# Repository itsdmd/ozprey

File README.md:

# Ozprey - A remix of [osprey-remix](https://github.com/kapee1/osprey-remix)

## Changes compared to the original Osprey

-   Remove cutout under MCU to allow more flexible PCB trace routing.
-   Remove battery holder cutout, replace onboard battery connector socket with battery connector pads.
    -   These changes were made since I want to use a large Li-Po battery placed under the PCB.
-   Simplify top edge, widen the split gap to accomodate changed switch footprint.
-   Replace power and reset switch footprint. Schematics for both can be found inside [img](./img) folder.
-   Adjust onboard M2 mounting holes' position.

These changes made the board incompatible with the original case & plate. You can get the [.STEP file](./ozprey_case/osprey_pcb.step) and design your own case & plate.

## Thanks

Huge thanks to [ebastler](https://github.com/ebastler), author of the [original project](https://github.com/ebastler/osprey) for the inspiration and design, and [kapee1](https://github.com/kapee1) for the nice!nano implementation with the [osprey-remix](https://github.com/kapee1/osprey-remix).

The keyboard switch footprint was from [daprice/keyswitches.pretty](https://github.com/daprice/keyswitches.pretty).

## Disclaimer

This is a **personal project** and not affiliated with the original authors. Due to the changes, the board is not compatible with the original case and plate.

The gerber file has been checked against JLCPCB's DFM checker and no critical error was found. All files are provided as-is, **without any warranty or support**. Use at your own risk.

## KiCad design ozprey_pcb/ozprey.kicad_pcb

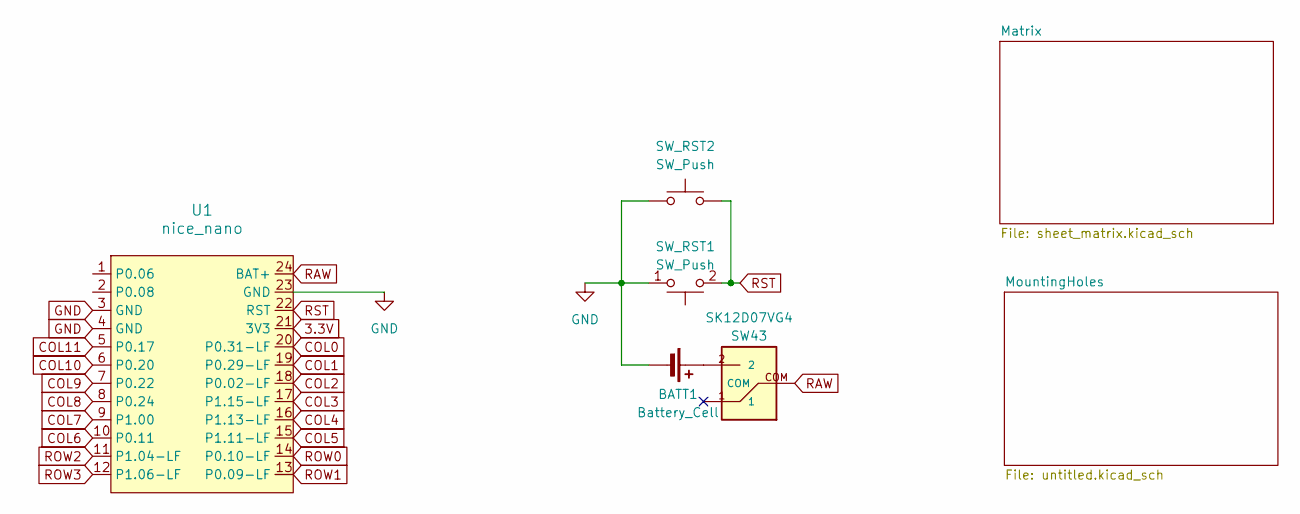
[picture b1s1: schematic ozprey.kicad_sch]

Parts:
BATT1: Battery_Cell; Battery_Pads-dual-side
SW43: SK12D07VG4; SW-S_SK12D07VG4
SW_RST1: SW_Push; SW-S_7.4x2.6-4pad-smd
SW_RST2: SW_Push; SW-T_SPST_TL3342
U1: nice_nano; MCB_nice-nano_flip

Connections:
3.3V: U1.21 (3V3)
COL0: U1.20 (P0.31-LF); also elsewhere on the board
COL1: U1.19 (P0.29-LF); also elsewhere on the board
COL2: U1.18 (P0.02-LF); also elsewhere on the board
COL3: U1.17 (P1.15-LF); also elsewhere on the board
COL4: U1.16 (P1.13-LF); also elsewhere on the board
COL5: U1.15 (P1.11-LF); also elsewhere on the board
COL6: U1.10 (P0.11); also elsewhere on the board
COL7: U1.9 (P1.00); also elsewhere on the board
COL8: U1.8 (P0.24); also elsewhere on the board
COL9: U1.7 (P0.22); also elsewhere on the board
COL10: U1.6 (P0.20); also elsewhere on the board
COL11: U1.5 (P0.17); also elsewhere on the board
GND: BATT1.2 (-), SW_RST1.1, SW_RST2.1, U1.3 (GND), U1.4 (GND), U1.23 (GND); also elsewhere on the board
unnamed: BATT1.1 (+), SW43.2
RAW: SW43.COM, U1.24 (BAT+)
ROW0: U1.14 (P0.10-LF); also elsewhere on the board
ROW1: U1.13 (P0.09-LF); also elsewhere on the board
ROW2: U1.11 (P1.04-LF); also elsewhere on the board
ROW3: U1.12 (P1.06-LF); also elsewhere on the board
RST: SW_RST1.2, SW_RST2.2, U1.22 (RST); also elsewhere on the board

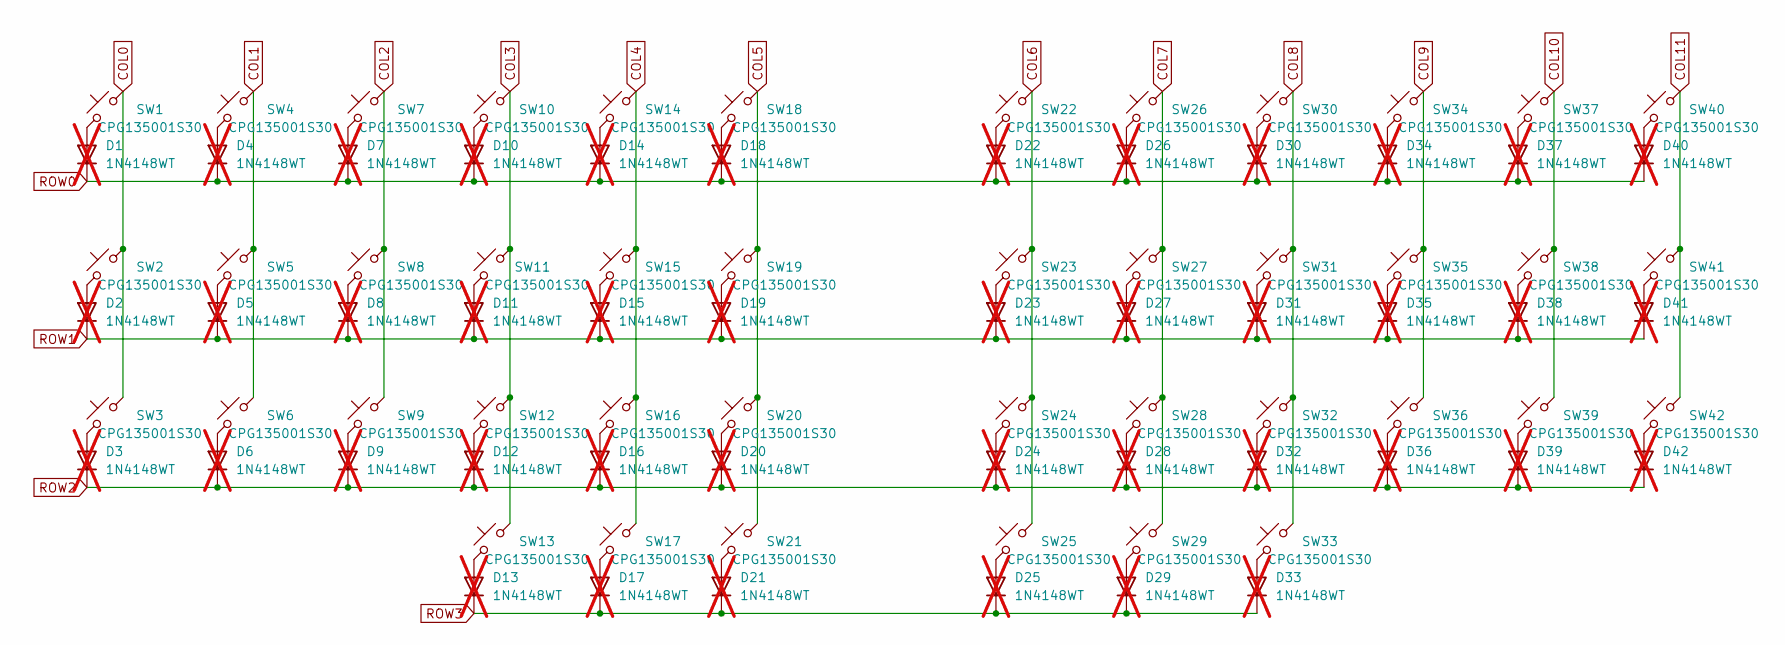
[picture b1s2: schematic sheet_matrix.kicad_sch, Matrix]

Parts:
D1, D2, D3, D4, D5, D6, D7, D8, D9, D10, D11, D12, D13, D14, D15, D16, D17, D18, D19, D20, D21, D22, D23, D24, D25, D26, D27, D28, D29, D30, D31, D32, D33, D34, D35, D36, D37, D38, D39, D40, D41, D42: 1N4148WT; D_SOD-123; not fitted
SW1, SW2, SW3, SW4, SW5, SW6, SW7, SW8, SW9, SW10, SW11, SW12, SW13, SW14, SW15, SW16, SW17, SW18, SW19, SW20, SW21, SW22, SW23, SW24, SW25, SW26, SW27, SW28, SW29, SW30, SW31, SW32, SW33, SW34, SW35, SW36, SW37, SW38, SW39, SW40, SW41, SW42: CPG135001S30; KS_Socket_Choc

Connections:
COL0: SW1.1, SW2.1, SW3.1; also elsewhere on the board
COL1: SW4.1, SW5.1, SW6.1; also elsewhere on the board
COL2: SW7.1, SW8.1, SW9.1; also elsewhere on the board
COL3: SW10.1, SW11.1, SW12.1, SW13.1; also elsewhere on the board
COL4: SW14.1, SW15.1, SW16.1, SW17.1; also elsewhere on the board
COL5: SW18.1, SW19.1, SW20.1, SW21.1; also elsewhere on the board
COL6: SW22.1, SW23.1, SW24.1, SW25.1; also elsewhere on the board
COL7: SW26.1, SW27.1, SW28.1, SW29.1; also elsewhere on the board
COL8: SW30.1, SW31.1, SW32.1, SW33.1; also elsewhere on the board
COL9: SW34.1, SW35.1, SW36.1; also elsewhere on the board
COL10: SW37.1, SW38.1, SW39.1; also elsewhere on the board
COL11: SW40.1, SW41.1, SW42.1; also elsewhere on the board
unnamed: D1.2 (A), SW1.2
unnamed: D2.2 (A), SW2.2
unnamed: D3.2 (A), SW3.2
unnamed: D4.2 (A), SW4.2
unnamed: D5.2 (A), SW5.2
unnamed: D6.2 (A), SW6.2
unnamed: D7.2 (A), SW7.2
unnamed: D8.2 (A), SW8.2
unnamed: D9.2 (A), SW9.2
unnamed: D10.2 (A), SW10.2
unnamed: D11.2 (A), SW11.2
unnamed: D12.2 (A), SW12.2
unnamed: D13.2 (A), SW13.2
unnamed: D14.2 (A), SW14.2
unnamed: D15.2 (A), SW15.2
unnamed: D16.2 (A), SW16.2
unnamed: D17.2 (A), SW17.2
unnamed: D18.2 (A), SW18.2
unnamed: D19.2 (A), SW19.2
unnamed: D20.2 (A), SW20.2
unnamed: D21.2 (A), SW21.2
unnamed: D22.2 (A), SW22.2
unnamed: D23.2 (A), SW23.2
unnamed: D24.2 (A), SW24.2
unnamed: D25.2 (A), SW25.2
unnamed: D26.2 (A), SW26.2
unnamed: D27.2 (A), SW27.2
unnamed: D28.2 (A), SW28.2
unnamed: D29.2 (A), SW29.2
unnamed: D30.2 (A), SW30.2
unnamed: D31.2 (A), SW31.2
unnamed: D32.2 (A), SW32.2
unnamed: D33.2 (A), SW33.2
unnamed: D34.2 (A), SW34.2
unnamed: D35.2 (A), SW35.2
unnamed: D36.2 (A), SW36.2
unnamed: D37.2 (A), SW37.2
unnamed: D38.2 (A), SW38.2
unnamed: D39.2 (A), SW39.2
unnamed: D40.2 (A), SW40.2
unnamed: D41.2 (A), SW41.2
unnamed: D42.2 (A), SW42.2
ROW0: D1.1 (K), D4.1 (K), D7.1 (K), D10.1 (K), D14.1 (K), D18.1 (K), D22.1 (K), D26.1 (K), D30.1 (K), D34.1 (K), D37.1 (K), D40.1 (K); also elsewhere on the board
ROW1: D2.1 (K), D5.1 (K), D8.1 (K), D11.1 (K), D15.1 (K), D19.1 (K), D23.1 (K), D27.1 (K), D31.1 (K), D35.1 (K), D38.1 (K), D41.1 (K); also elsewhere on the board
ROW2: D3.1 (K), D6.1 (K), D9.1 (K), D12.1 (K), D16.1 (K), D20.1 (K), D24.1 (K), D28.1 (K), D32.1 (K), D36.1 (K), D39.1 (K), D42.1 (K); also elsewhere on the board
ROW3: D13.1 (K), D17.1 (K), D21.1 (K), D25.1 (K), D29.1 (K), D33.1 (K); also elsewhere on the board

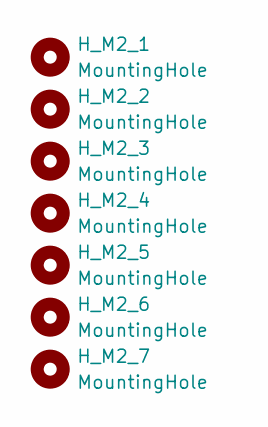
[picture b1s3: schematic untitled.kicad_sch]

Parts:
H_M2_1, H_M2_2, H_M2_3, H_M2_4, H_M2_5, H_M2_6, H_M2_7: MountingHole; MountingHole_2.2mm_M2

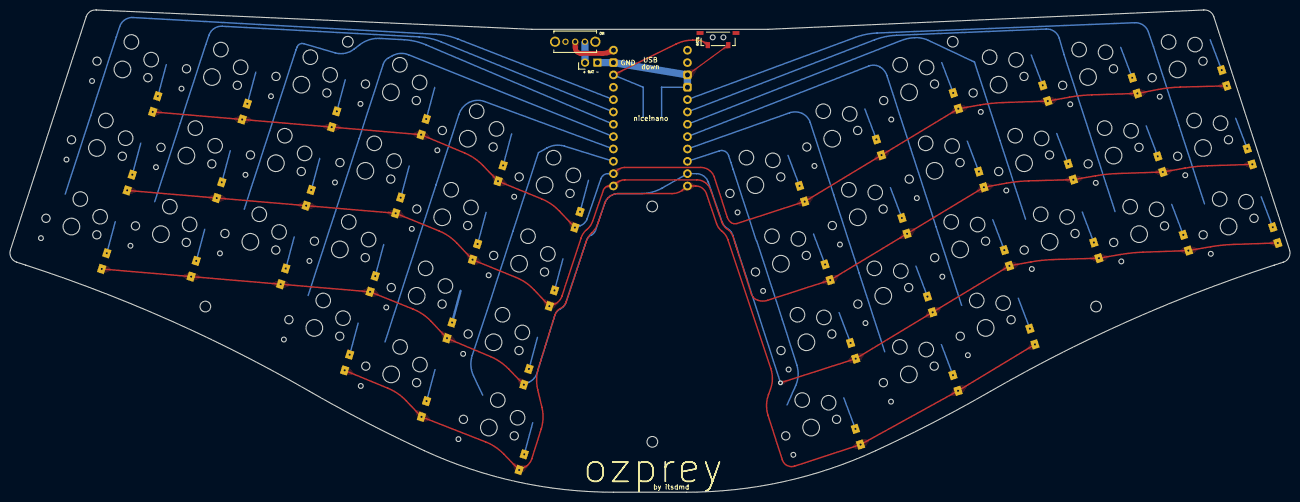
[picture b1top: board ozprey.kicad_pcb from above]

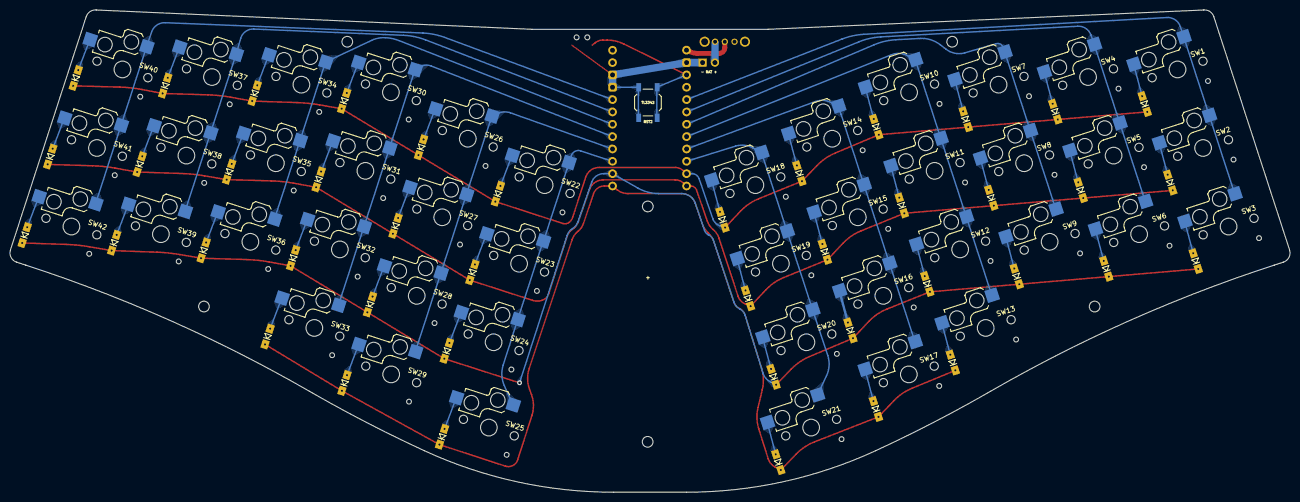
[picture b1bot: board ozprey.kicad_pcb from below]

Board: 2 copper layers, 263.5 x 99.3 mm, 95 parts (43 on the bottom side), 62 nets.

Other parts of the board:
RST2: SW_Push; SW-T_SPST_TL3342

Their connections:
GND: RST2.1; also elsewhere on the board
RST: RST2.2; also elsewhere on the board

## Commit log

2024-08-25 rename
2024-08-25 rework pcb, remove enclosure & plate folders
2024-08-25 update doc
2024-08-25 add gerber
2024-08-25 update m2 holes pos
2024-08-25 update img
2024-08-25 replace power & reset switches
2024-08-25 beautify
2024-09-01 major changes, add plate
2024-09-01 update images
2024-09-01 add plate image
